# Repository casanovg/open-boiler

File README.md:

# 
This project aims to replace a Roca Victoria 20/20T domestic combined boiler control PCB with an open-hardware/software alternative. It is possible that in the future its application will also be extended to other boiler models and manufacturers. \[[Español](LEEME.md)\] 

Take a look at it working: 
* [Domestic hot water and safety test](https://youtu.be/deHfOc_8mxE)
* Central Heating test: [room thermostat activation](https://youtu.be/CYksFCGb7gs) and [heating and water recirculation](https://youtu.be/nZ2wHWD1Drg)

<table>
<tbody>
	<tr>
		<td></td>
    <td></td>
  </tr>
  
</tbody>
</table>

## The story behind the project
I bought this “[Roca Victoria 20/20T](https://github.com/casanovg/open-boiler/blob/master/electronics/datasheets/Roca-Victoria-Technical-Manual.pdf)” combined boiler back in 2002 and it worked perfectly for approximately 5 years, then the first problems with the control sensors appeared. First was the ionization probe, which detects when the burner is on. Over time the exhaust gas flow meter also started to fail. It is interesting to mention that the failure of the first sensor leaves the boiler with an error indication waiting for a reset, so if this happens to you in the middle of a cold winter night when you sleep, in the morning you get up at the trans-Siberian express.

The other sensor, which checks if the combustion fume extractor generates pressure in the outlet pipe, has a bad habit of failing just when you are taking a nice warm bath, so that the cold water punch you receive when the boiler suddenly turns off with error makes you change the note that you were singing in the shower for a desperate scream worthy of a B-class horror movie. That's how I kept replacing the sensors, which are not cheap, regularly every 2 or three years.

After searching in various forums and websites, I concluded in principle that this boiler model was a nightmare and that I had to spend a significant sum of money to replace it and achieve peace of mind. But then I was sure that nothing guarantees that a new boiler does not start with the same problems in about 5 years since, searching a little, I found that these equipment's sensors seem to be a standard that, are more or less, common to all boiler manufacturers. So I kept “patching” the sensors' problems as they arose until, one day in July 2019, the [control board](https://github.com/casanovg/open-boiler/blob/media/pictures/roca-victoria-20-20-pcb.jpg) said “enough” and needed to be replaced, or buy a new boiler. The PCB, without sensors, costs nothing less than about USD 330 where I live, and a new boiler about USD 1.500.

Before throwing the boiler away, I decided to take it apart once more to see what I could do. I found that,  beyond the dislike of a boiler that had left me without DHW and central heating, I could appreciate in detail that the mechanical built was, indeed, quite well made. Noble materials, stainless steel, copper, good finishes. No water leakage, and not even a spot of rust in 17 years. So, tired of the electronics and sensors of this boiler, I decided to try to replace the control PCB with one made by myself, and therefore being able to take control of the installed components and, above all, the boiler firmware, to be able to decide when and how this gadget must stop with an unrecoverable error, or inform and move on when it is not something so serious. The idea is to be able to ensure that when a problem is detected, it is a problem (lack of gas, the flame extinguished by the wind, etc.) and not a sensor failure that detects it.

## Opening the black box
The first thing to consider is to start seeing the boiler, not as a black box any longer (or rather white in this case), but as a set of inputs and outputs to which you have to apply logic to make it work orchestrated. This particular boiler model is composed as follows:

## Inputs:
1. DHW temperature sensor: [Honeywell T7335D NTC thermistor (10 KΩ at 25 °C)](https://github.com/casanovg/open-boiler/blob/master/electronics/datasheets/T7335A-BCDE-series.pdf).
2. Central heating temperature sensor: [Honeywell T7335D NTC thermistor (10 KΩ at 25 °C)](https://github.com/casanovg/open-boiler/blob/master/electronics/datasheets/T7335A-BCDE-series.pdf).
3. DHW temperature setting: [Piher 10 KΩ through-hole PCB potentiometer](https://github.com/casanovg/open-boiler/blob/master/electronics/datasheets/Piher-PT15NV_10K_A2020.pdf).
4. DC temperature setting: [Piher 10 KΩ through-hole PCB potentiometer](https://github.com/casanovg/open-boiler/blob/master/electronics/datasheets/Piher-PT15NV_10K_A2020.pdf).
5. System mode setting: [Piher 10 KΩ through-hole PCB potentiometer](https://github.com/casanovg/open-boiler/blob/master/electronics/datasheets/Piher-PT15NV_10K_A2020.pdf).
6. Flame sensor: ionization probe -> to be replaced by a [KY-026](https://github.com/casanovg/open-boiler/blob/master/electronics/datasheets/KY-026.pdf) infrared light sensor module.
7. Flue exhaust flow sensor: [Pressure switch 12-15 mm ca](https://github.com/casanovg/open-boiler/blob/media/pictures/presostato-victoria-20-20-f.jpg) -> initially preserved but with an overridding option by software. Maybe it will be replaced by a Bosch BMP280 barometric sensor in the future.
8. Overheating sensor: [Campini Ty60R 105 °C manual reset-thermostat](https://github.com/casanovg/open-boiler/blob/master/electronics/datasheets/Campini-TY60R.pdf).
9. DHW request [magnetic detector](https://github.com/casanovg/open-boiler/blob/media/pictures/kit-captador-flow-switch-victoria-20-20.jpg).
10. Roca CH [room thermostat](https://github.com/casanovg/open-boiler/blob/media/pictures/room-thermostat-tm-1.jpg).

## Outputs:
1. Safety gas valve: Solenoid 12 VDC, 31 Ω.
2. 7.000 Kcal/h gas valve: Solenoid 12 VDC, 31 Ω.
3. 12.000 Kcal/h gas valve: Solenoid 12 VDC, 31 Ω.
4. 20.000 Kcal/h gas valve: Solenoid 12 VDC, 31 Ω.
5. Flue gas extractor: 220 VAC electric fan.
6. Heating water pump: 3-speed 220 VAC electric pump.
6. Electronic spark igniter: 18,000 V output, 12 and 5 VDC inputs.

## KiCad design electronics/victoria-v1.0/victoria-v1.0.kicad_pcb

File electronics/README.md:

### NOTE:
The schematics and board files were created with [KiCad](http://www.kicad-pcb.org), a highly recommendable open source EDA software supported by CERN (among others).
You need to install it on your computer to use the files under the "victoria-control" folder.

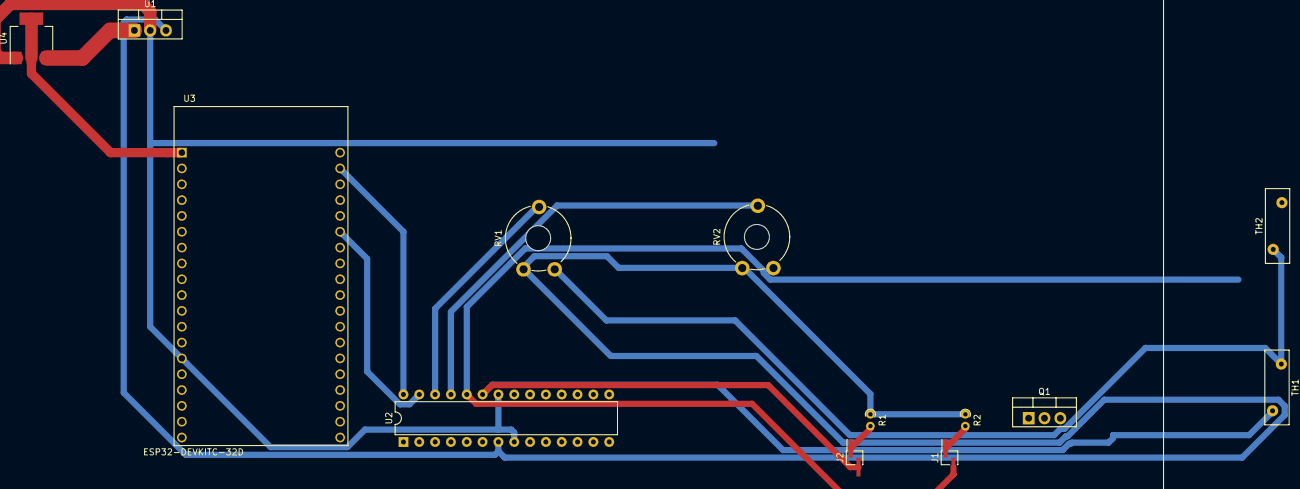
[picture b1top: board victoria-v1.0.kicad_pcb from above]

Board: 2 copper layers, 13 parts (0 on the bottom side), 12 nets.

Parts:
J1, J2: Conn_01x02; PinHeader_1x02_P1.27mm_Vertical_SMD_Pin1Right
Q1: Q_NMOS_GDS; TO-220-3_Vertical
R1, R2: 10K; R_Axial_DIN0204_L3.6mm_D1.6mm_P1.90mm_Vertical
RV1, RV2: 10K; Potentiometer_Piher_PT-10-V10_Vertical_Hole
TH1, TH2: Thermistor_NTC; RV_Disc_D12mm_W3.9mm_P7.5mm
U1: LM7805_TO220; TO-220-3_Vertical
U2: ATmega328P-PU; DIP-28_W7.62mm
U3: ESP32-DEVKITC-32D; MODULE_ESP32-DEVKITC-32D
U4: AMS1117-3.3; SOT-223-3_TabPin2

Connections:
+3V3: U3.1, U4.2
+5V: R1.1, R2.1, RV1.3, RV2.3, U1.3, U2.7
+12V: U1.1, U4.3
CH-Pot: RV1.2, U2.26
CH-Sensor: J1.2, TH2.1, U2.24
DHW-Pot: RV2.2, U2.25
DHW-Sensor: J2.2, TH1.1, U2.23
GND: RV1.1, RV2.1, TH1.2, TH2.2, U1.2, U2.8, U2.22, U3.14, U4.1
unnamed: J1.1, R2.2
unnamed: J2.1, R1.2
SCL: U2.28, U3.21
SDA: U2.27, U3.25

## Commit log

2019-09-22 First functional test v0.5
2019-09-22 Release v0.5
2019-10-06 Release 06a
2019-10-07 Add PROYECTO.md file
2019-10-07 Update README.md and LEEME.md.
2019-10-09 Media initial commit
2019-10-09 Testbed initial commit
2019-10-12 Version 0.7 initial commit
2019-10-12 Update .sconsign.dblite, delays.h, and 3 more files...
2019-10-13 Update .gitignore, HISTORIA.md, and 2 more files...
2019-10-13 Update .sconsign.dblite, project.checksum, and 2 more files...
2019-10-13 Update .sconsign.dblite, settings.json, and 2 more files...
2019-10-14 Add ADC average calculation function
2019-10-15 Add ADC values preload on start
2019-10-15 Fix ADC buffers overflow
2019-10-15 Update .gitignore, .sconsign.dblite, and 3 more files...
2019-10-16 Add robust and moving average calculations
2019-10-17 Update Open-Boiler.xlsx, ~$Open-Boiler.xlsx, and 2 more files...
2019-10-19 Add Tst-02 to solve temperature calculation
2019-10-25 Add FAN_TEST_OVERRIDE compilation option
2019-10-28 Add GetHeatLevel function
2019-11-10 Add first version of modulation code - NOT WORKING
2019-11-11 Heat modulation code compiles - NOT TESTED
2019-11-12 Add hardware mapping header, move constants to flash memory ...
2019-11-13 Heat modulation code ready for first test
2019-11-15 Operating tests: UNSUCCESSFUL
2019-11-15 Set summer DHW temp -> only valve-1
2019-11-17 Add victoria-control-as7 Atmel Studio version
2019-11-18 Minor label changes
2019-11-19 Start test-03 development
2019-11-19 Add bootloaders folder
2019-11-19 Update .sconsign.py37.dblite, project.checksum, and 3 more files...
2019-11-20 Test timing on tst-03
2019-11-20 Add a 3-second gap between heat levels in tst-03
2019-11-24 Add tst-04 folder
2019-11-26 Update .sconsign.py37.dblite, project.checksum, and 2 more files...
2020-03-01 Implement modified version daiplay
2020-03-01 Update version display in experimental version test-04
2020-03-02 Add v0.7 schematic pdf
2020-03-07 Update .sconsign.py37.dblite, project.checksum, and 7 more files...
2020-03-08 Update .sconsign.py27.dblite, .sconsign.py37.dblite, and 5 more files...
2020-03-09 Update .sconsign.py27.dblite, .sconsign.py37.dblite, and 14 more files...
2020-03-12 Add arduino pro mini bootloaders folder
2020-03-13 Update 1N4007.pdf, 432-Manual-Reset-Snap-Disc-Thermostat.pdf, and 90 more files...
2020-03-30 Update flash-arduino-bootloader-avrdude.sh, flash-optiboot-bootloader-avrdude.sh, and 5 more files...
2020-04-01 Update tst-01.c, .sconsign.py37.dblite, and 21 more files...
2020-04-01 Implement heat modulator: first version OK!
2020-04-01 Improve heat modulation by reducing useless valve-toggling
2020-04-06 Update .sconsign.py37.dblite, victoria-control.h, and 13 more files...
2020-04-09 Update Makefile, flash-gc-avrdude.sh, and 15 more files...
2020-04-09 Update .sconsign.py37.dblite, .gitignore, and 29 more files...
2020-04-09 Release v0.7
2020-04-09 Update project.checksum, c_cpp_properties.json, and 2 more files...
2020-04-10 v0.8 heat modulation first test
2020-04-12 Refactor version 0.8
2020-04-12 Replace FSM timing for new timer library functions (Constructions: if (!(delay--)) -> if (TimerFinished(FSM_TIMER_ID)) /// delay = DLY_READY_1 --> ResetTimerLapse(FSM_TIMER_ID, DLY_READY_1))
2020-04-13 Fix some FSM DHW_ON_DUTY bugs
2020-04-13 Rename ModulateGas function to OpenHeatValve ...
2020-04-14 Fix new heat modulation code in CH_ON_DUTY state
2020-04-15 Modify switch debounce code to use system timers
2020-04-15 Update .gitignore files
2020-04-16 Rename system_mode potentiometer code
2020-04-16 Rename system_mode variable
2020-04-17 Implement system mode code
2020-04-17 Update .gitignore, .travis.yml, and 11 more files...
2020-04-17 Keep only one v0.7 version
2020-04-17 Synchronize master v0.7 version with latest testbed updates
2020-04-17 Update .gitignore, project.checksum, and 11 more files...
2020-04-18 Update victoria-control.c, .gitignore, and 20 more files...
2020-04-18 Rename InvertFlag function to ToggleFlag
2020-04-18 Update hal.c, hal.h, and 6 more files...
2020-04-18 Update timers.c, timers.h, and 3 more files...
2020-04-19 Test water pump timing in Tst-07
2020-04-19 Fix timers library minor bugs
2020-04-19 Change timers unsigned long types for uint32_t
2020-04-19 Update Tst-07 pump codeto use timers ...
2020-04-19 Implement v0.8 water pump timing with system timers
2020-04-19 Fix DHW_ON_DUTY no pump shutdown bug
2020-04-19 ADC naming redefinition on v0.8
2020-04-19 Increase pump timer
2020-04-19 long integer type redefinitions
2020-04-20 Improve temperature display in serial UI v0.8
2020-04-20 Correct pump shutdown timer and dashboard temperature display
2020-04-20 Add test output file [Com COM3] (2020-04-20_010503).log
2020-04-21 Add FTDI pinout
2020-04-21 reduce DHW_HEAT_CYCLE_TIME to 15 seconds
2020-04-22 Fix several small issues and adjust FSM ignition timing
2020-04-22 Streamline the flame ignition code in v0.8
2020-04-23 Adjust igniting timing, add ignition retries to dashboard
2020-04-23 Add a line for ignition retries = 0 if ignition request is over before going to ready state
2020-04-23 Tidy up dashboard literals
2020-04-24 Update sys-settings.h, hal.c, and 2 more files...
2020-04-24 Implement v0.8 Release Candidate 1: Short-lapse pump activation in DHW mode to avoid CH water overheat, selectable dashboard display, minor dashboard adjustments
2020-04-24 Tidy up software tests
2020-04-25 Improve temperature display in the dashboard in v0.8
2020-04-25 Fix CH temperature display variable
2020-04-25 Make autorefresh definitions conditional
2020-04-26 Implement v0.8 dashboard localization
2020-04-26 Setup MobaXTerm coloring for Open-Boiler v0.8
2020-04-26 Release v0.8
2020-04-26 Change "Thermostat" label in Spanish dashboard
2020-04-26 Add ADC safety readout thresholds to improve NTC sensors failure detection
2020-04-26 Update sys-settings.h
    Set English dashboard language
2020-04-26 Set English dashboard language
2020-04-26 Add boiler and software dashboard pictures
2020-04-27 Add sensors datasheets
2020-04-27 Add boiler parts pictures
2020-04-27 Add room thermostat pics
2020-04-27 Update ATmega48A-PA-88A-PA-168A-PA-328-P-DS-DS40002061A.pdf, KY-026.pdf, and 2 more files...
2020-04-27 Update sys-settings.h, hal.h, and 4 more files...
2020-04-27 Adjust dates
2020-04-27 Fix v0.7 labels
2020-04-27 Update pictures
2020-04-27 Update ATmega48A-PA-88A-PA-168A-PA-328-P-DS-DS40002061A.pdf, MAC8M.pdf, and 6 more files...
2020-04-27 Update MobaXterm syntax color highlighting file
2020-05-04 Update .gitignore, .travis.yml, and 18 more files...
2020-05-05 Add readme in software folder
2020-05-12 Add spark igniter rare component pics
2020-05-12 Move software tests to PlatformIO
2020-05-13 Implement avr-blink-twis as Tst-08
2020-05-13 Update avr-blink-twis.h, LICENSE, and 16 more files...
2020-05-13 Update nb-twisl.c, nb-twisl.h, and 4 more files...
2020-05-14 Update Arduino Pro Mini pinout-Deek Robot.pdf, ArduinoProMini-DeekRobot.jpg, and 5 more files...
2020-06-15 Update .gitignore, .travis.yml, and 6 more files...
2020-07-03 Update KY-026-Joy-IT.pdf, flash-timonel-bootloader.sh, and 170 more files...
2020-07-03 Setup ATMega328P to reset correctly
2020-07-17 Remove underscores from header guard macros and add firmware start indication
2020-07-17 Prepare GasOff function and its calls for debugging on a separate v0.8-d version folder
2020-07-17 Reduce start indication blink delay
2020-07-18 Add GASOFF_DEBUG preprocessor macro
2020-07-18 Fix bootloaader and fuse flashing scripts
2020-07-18 Fix preprocessor macro comment
2020-10-06 Update scripts Tue 06 Oct 2020 01:57:03 AM -03
2021-05-19 Add pdf schematic
2021-06-22 Add fuse settings to platformio.ini and create 2 different envs (with/wthout bootloader)
2022-06-04 Add KiCad libraries folder readme
2022-06-05 Update schematic to KiCad 6
2022-06-05 Update project symbol libraries to KiCad 6
2022-06-05 Update fp-info-cache, fp-lib-table, and 3 more files...
2022-06-05 Add fuses to mains-connected motor circuits
2023-11-10 Add v0.8 reverse flame detector version
2023-11-10 Update v 0.8 reverse flame detection version
2025-07-05 Add module flashing details and pictures
2025-07-05 Update flash script
